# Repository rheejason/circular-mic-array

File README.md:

# Circular Beamforming Microphone Array

UIUC ECE 395: an 8-mic circular beamforming microphone array (steerable conference-table mic
and acoustic imager).

| Folder | What | Tooling |
|---|---|---|
| `firmware/nucleo-proto/` | Bench prototype: NUCLEO-H753ZI + 4 Adafruit PDM mics on a 3D-printed 45 mm ring | STM32CubeIDE |
| `firmware/final/` | Firmware for the custom 8-mic STM32H743 board | STM32CubeIDE |
| `firmware/common/` | Hardware-independent C shared by both: DOA (GCC-PHAT), beamformer, ring buffer | CMSIS-DSP |
| `hardware/kicad/` | 8-mic board: 8 × T5838 PDM mics → ADAU7118 → STM32H743 SAI | KiCad |
| `hardware/mechanical/` | Bench rig mount and enclosure (STEP / 3MF exports) | Fusion 360 |
| `hardware/bom/` | Bills of materials | |

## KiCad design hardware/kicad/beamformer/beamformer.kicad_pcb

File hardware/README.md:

# Hardware

| Folder | What |
|---|---|
| `kicad/` | 8-mic board KiCad project |
| `mechanical/` | Bench rig ring and enclosure: STEP and 3MF exports (keep the Fusion source link in a note here) |
| `bom/` | Bills of materials |
| `layout-checklist.md` | What's left before and during PCB layout, and before ordering |

## 8-mic board (planned)

- 8 × TDK InvenSense T5838 (MMICT5838-00-012), bottom port, uniform circle, radius 55 mm (tentative).
  Each mic needs a 0.5–1 mm PCB hole; the hole centre is the mic's acoustic position.
- 2 mics per PDM data line (opposite SELECT), 4 lines into an ADAU7118 → TDM8 → STM32H743 SAI.
- PDM clock 3.072 MHz (÷64 = 48 kHz).
- Still to decide: LCD part (round GC9A01 planned), LED ring, enclosure, which mics share a data line.
- Check in the datasheets before layout: ADAU7118 clocking and PDM clock fan-out, T5838 mode/threshold pins.

## KiCad

Schematic and PCB files don't merge, so only one person edits a sheet or board at a time.
Pull before opening KiCad and push when you're done.

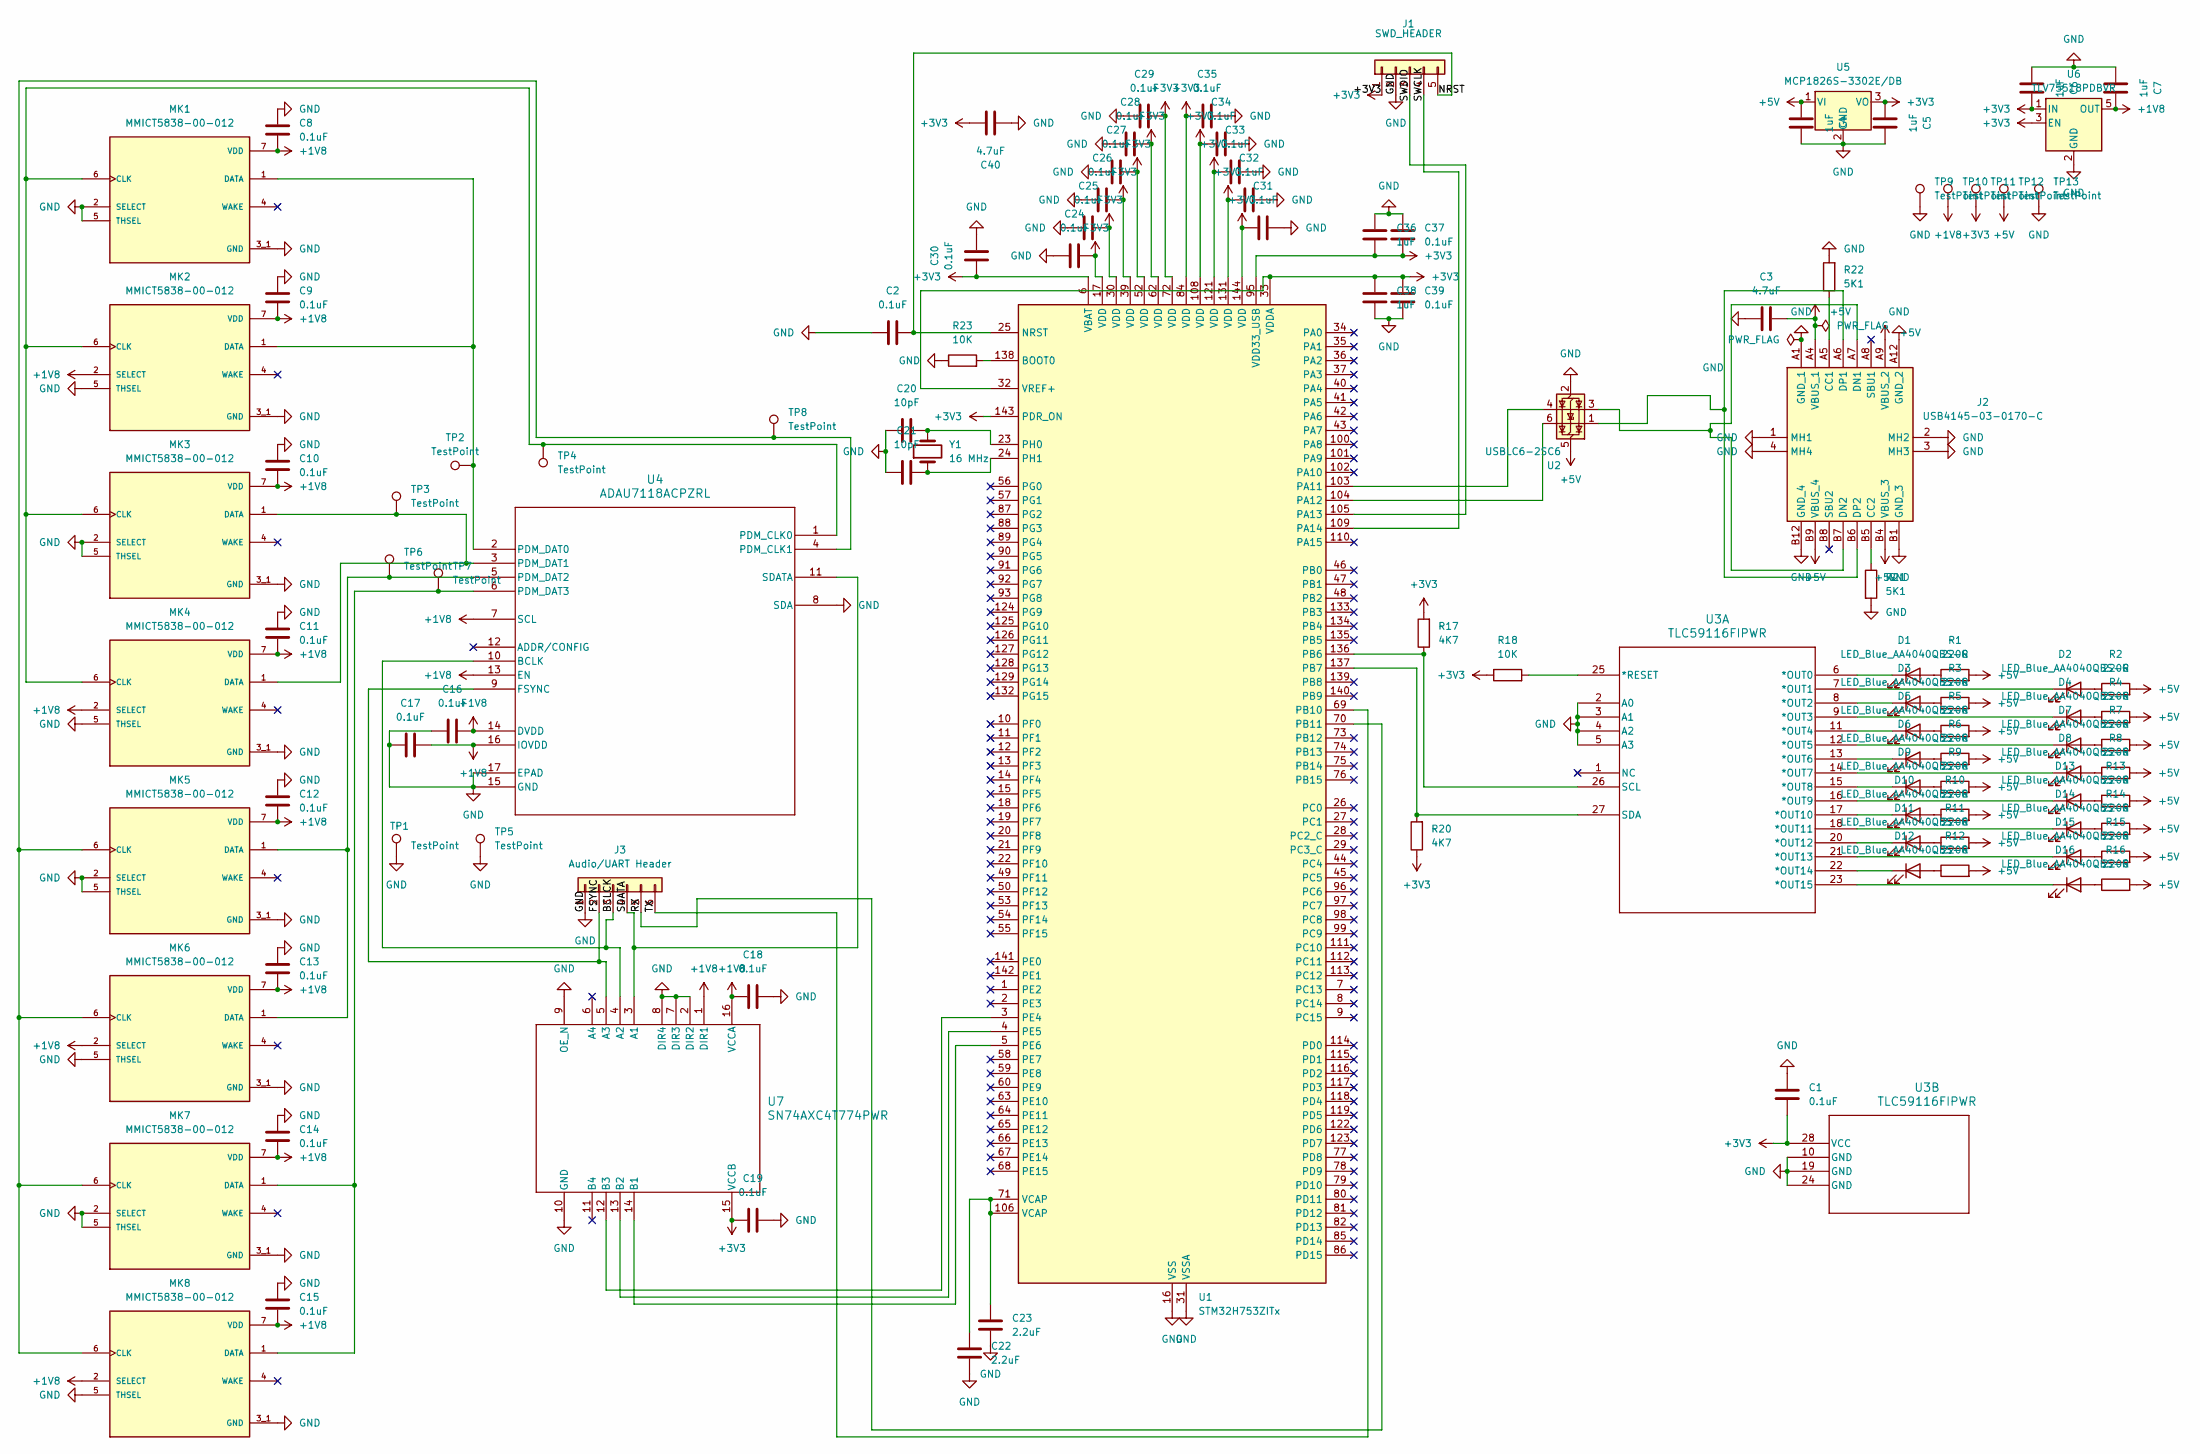
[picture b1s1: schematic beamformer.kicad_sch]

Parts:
C1, C2, C8, C9, C10, C11, C12, C13, C14, C15, C16, C17, C18, C19, C24, C25, C26, C27, C28, C29, C30, C31, C32, C33, C34, C35, C37, C39: 0.1uF; C_0805_2012Metric
C3, C40: 4.7uF; C_0805_2012Metric
C4, C5, C6, C7, C36, C38: 1uF; C_0805_2012Metric
C20, C21: 10pF; C_0805_2012Metric
C22, C23: 2.2uF; C_0805_2012Metric
D1, D2, D3, D4, D5, D6, D7, D8, D9, D10, D11, D12, D13, D14, D15, D16: LED_Blue_AA4040QBS-G; LED_Kingbright_AA4040QBS-G
J1: SWD_HEADER; PinHeader_1x05_P2.54mm_Vertical
J2: USB4145-03-0170-C; CONN_USB4145-03-0230-C_GCT; Manufacturer_Part_Number USB4145-03-0170-C; Mouser Part Number 640-USB4145-3-0170-C
J3: Audio/UART Header; PinHeader_1x06_P2.54mm_Vertical
MK1, MK2, MK3, MK4, MK5, MK6, MK7, MK8: MMICT5838-00-012; MIC_MMICT5838-00-012; PARTREV 1.1
R1, R2, R3, R4, R5, R6, R7, R8, R9, R10, R11, R12, R13, R14, R15, R16: 220R; R_0805_2012Metric
R17, R20: 4K7; R_0805_2012Metric
R18, R23: 10K; R_0805_2012Metric
R21, R22: 5K1; R_0805_2012Metric
TP1, TP2, TP3, TP4, TP5, TP6, TP7, TP8, TP9, TP10, TP11, TP12, TP13: TestPoint; TestPoint_Pad_D1.5mm
U1: STM32H753ZITx; LQFP-144_20x20mm_P0.5mm
U2: USBLC6-2SC6; SOT-23-6
U3: TLC59116FIPWR; TSSOP-28_4.4x9.7mm_P0.65mm
U4: ADAU7118ACPZRL; CP-16-22_ADI
U5: MCP1826S-3302E/DB; SOT-223-3_TabPin2
U6: TLV75518PDBVR; SOT-23-5
U7: SN74AXC4T774PWR; TSSOP-16_4.4x5mm_P0.65mm
Y1: 16 MHz; ECS-160-8-30Q-VY-TR

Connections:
+1V8: C7.2, C8.1, C9.1, C10.1, C11.1, C12.1, C13.1, C14.1, C15.1, C16.1, C17.1, C18.2, MK1.7 (VDD), MK2.2 (SELECT), MK2.7 (VDD), MK3.7 (VDD), MK4.2 (SELECT), MK4.7 (VDD), MK5.7 (VDD), MK6.2 (SELECT), MK6.7 (VDD), MK7.7 (VDD), MK8.2 (SELECT), MK8.7 (VDD), TP10.1 (1_1), U4.7 (SCL), U4.13 (EN), U4.14 (DVDD), U4.16 (IOVDD), U6.5 (OUT), U7.1 (DIR1), U7.16 (VCCA)
+3V3: C1.2, C5.1, C6.2, C19.2, C24.2, C25.2, C26.2, C27.2, C28.2, C29.2, C30.1, C31.2, C32.2, C33.2, C34.2, C35.2, C36.2, C37.2, C38.1, C39.1, C40.2, J1.1, R17.2, R18.1, R20.1, TP11.1 (1_1), U1.6 (VBAT), U1.17 (VDD), U1.30 (VDD), U1.32 (VREF+), U1.33 (VDDA), U1.39 (VDD), U1.52 (VDD), U1.62 (VDD), U1.72 (VDD), U1.84 (VDD), U1.95 (VDD33_USB), U1.108 (VDD), U1.121 (VDD), U1.131 (VDD), U1.143 (PDR_ON), U1.144 (VDD), U3.28 (VCC), U5.3 (VO), U6.1 (IN), U6.3 (EN), U7.15 (VCCB)
+5V: C3.2, C4.1, J2.A4 (VBUS_1), J2.A9 (VBUS_2), J2.B4 (VBUS_3), J2.B9 (VBUS_4), R1.2, R2.2, R3.2, R4.2, R5.2, R6.2, R7.2, R8.2, R9.2, R10.2, R11.2, R12.2, R13.2, R14.2, R15.2, R16.2, TP12.1 (1_1), U2.5 (VBUS), U5.1 (VI)
/BCLCK: J3.3, U4.10 (BCLK), U7.4 (A2)
/FSYNC: J3.2, U4.9 (FSYNC), U7.5 (A3)
/NRST: C2.2, J1.5, U1.25 (NRST)
/RX: J3.5, U1.70 (PB11)
/SDATA: J3.4, U4.11 (SDATA), U7.3 (A1)
/SWCLK: J1.4, U1.109 (PA14)
/SWDIO: J1.3, U1.105 (PA13)
/TX: J3.6, U1.69 (PB10)
GND: C1.1, C2.1, C3.1, C4.2, C5.2, C6.1, C7.1, C8.2, C9.2, C10.2, C11.2, C12.2, C13.2, C14.2, C15.2, C16.2, C17.2, C18.1, C19.1, C20.1, C21.1, C22.2, C23.2, C24.1, C25.1, C26.1, C27.1, C28.1, C29.1, C30.2, C31.1, C32.1, C33.1, C34.1, C35.1, C36.1, C37.1, C38.2, C39.2, C40.1, J1.2, J2.1 (MH1), J2.2 (MH2), J2.3 (MH3), J2.4 (MH4), J2.A1 (GND_1), J2.A12 (GND_2), J2.B1 (GND_3), J2.B12 (GND_4), J3.1, MK1.2 (SELECT), MK1.3_1 (GND), MK1.3_2 (GND), MK1.5 (THSEL), MK2.3_1 (GND), MK2.3_2 (GND), MK2.5 (THSEL), MK3.2 (SELECT), MK3.3_1 (GND), MK3.3_2 (GND), MK3.5 (THSEL), MK4.3_1 (GND), MK4.3_2 (GND), MK4.5 (THSEL), MK5.2 (SELECT), MK5.3_1 (GND), MK5.3_2 (GND), MK5.5 (THSEL), MK6.3_1 (GND), MK6.3_2 (GND), MK6.5 (THSEL), MK7.2 (SELECT), MK7.3_1 (GND), MK7.3_2 (GND), MK7.5 (THSEL), MK8.3_1 (GND), MK8.3_2 (GND), MK8.5 (THSEL), R21.2, R22.2, R23.1, TP1.1 (1_1), TP5.1 (1_1), TP9.1 (1_1), TP13.1 (1_1), U1.16 (VSS), U1.31 (VSSA), U1.38 (VSS), U1.51 (VSS), U1.61 (VSS), U1.83 (VSS), U1.94 (VSS), U1.107 (VSS), U1.120 (VSS), U1.130 (VSS), U2.2 (GND), U3.2 (A0), U3.3 (A1), U3.4 (A2), U3.5 (A3), U3.10 (GND), U3.19 (GND), U3.24 (GND), U4.8 (SDA), U4.15 (GND), U4.17 (EPAD), U5.2 (GND), U6.2 (GND), U7.2 (DIR2), U7.7 (DIR3), U7.8 (DIR4), U7.9 (OE_N), U7.10 (GND)
unnamed: C22.1, C23.1, U1.71 (VCAP), U1.106 (VCAP)
unnamed: D1.2 (A), R1.1
unnamed: D1.1 (K), U3.6 (*OUT0)
unnamed: D2.2 (A), R2.1
unnamed: D2.1 (K), U3.7 (*OUT1)
unnamed: D3.2 (A), R3.1
unnamed: D3.1 (K), U3.8 (*OUT2)
unnamed: D4.2 (A), R4.1
unnamed: D4.1 (K), U3.9 (*OUT3)
unnamed: D5.2 (A), R5.1
unnamed: D5.1 (K), U3.11 (*OUT4)
unnamed: D6.2 (A), R6.1
unnamed: D6.1 (K), U3.13 (*OUT6)
unnamed: D7.2 (A), R7.1
unnamed: D7.1 (K), U3.12 (*OUT5)
unnamed: D8.2 (A), R8.1
unnamed: D8.1 (K), U3.14 (*OUT7)
unnamed: D9.2 (A), R9.1
unnamed: D9.1 (K), U3.15 (*OUT8)
unnamed: D10.2 (A), R10.1
unnamed: D10.1 (K), U3.17 (*OUT10)
unnamed: D11.2 (A), R11.1
unnamed: D11.1 (K), U3.20 (*OUT12)
unnamed: D12.2 (A), R12.1
unnamed: D12.1 (K), U3.22 (*OUT14)
unnamed: D13.2 (A), R13.1
unnamed: D13.1 (K), U3.16 (*OUT9)
unnamed: D14.2 (A), R14.1
unnamed: D14.1 (K), U3.18 (*OUT11)
unnamed: D15.2 (A), R15.1
unnamed: D15.1 (K), U3.21 (*OUT13)
unnamed: D16.2 (A), R16.1
unnamed: D16.1 (K), U3.23 (*OUT15)
unnamed: J2.A5 (CC1), R22.1
unnamed: J2.B5 (CC2), R21.1
unnamed: J2.A7 (DN1), J2.B7 (DN2), U2.3 (I/O2)
unnamed: J2.A6 (DP1), J2.B6 (DP2), U2.1 (I/O1)
unnamed: MK1.6 (CLK), MK2.6 (CLK), MK3.6 (CLK), MK4.6 (CLK), TP4.1 (1_1), U4.1 (PDM_CLK0)
unnamed: MK1.1 (DATA), MK2.1 (DATA), TP2.1 (1_1), U4.2 (PDM_DAT0)
unnamed: MK3.1 (DATA), MK4.1 (DATA), TP3.1 (1_1), U4.3 (PDM_DAT1)
unnamed: MK5.6 (CLK), MK6.6 (CLK), MK7.6 (CLK), MK8.6 (CLK), TP8.1 (1_1), U4.4 (PDM_CLK1)
unnamed: MK5.1 (DATA), MK6.1 (DATA), TP6.1 (1_1), U4.5 (PDM_DAT2)
unnamed: MK7.1 (DATA), MK8.1 (DATA), TP7.1 (1_1), U4.6 (PDM_DAT3)
unnamed: R23.2, U1.138 (BOOT0)
unnamed: U1.103 (PA11), U2.4 (I/O2)
unnamed: U1.104 (PA12), U2.6 (I/O1)
unnamed: R17.1, U1.136 (PB6), U3.26 (SCL)
unnamed: R20.2, U1.137 (PB7), U3.27 (SDA)
unnamed: U1.3 (PE4), U7.12 (B3)
unnamed: U1.4 (PE5), U7.13 (B2)
unnamed: U1.5 (PE6), U7.14 (B1)
unnamed: C20.2, U1.23 (PH0), Y1.2
unnamed: C21.2, U1.24 (PH1), Y1.1
unnamed: R18.2, U3.25 (*RESET)

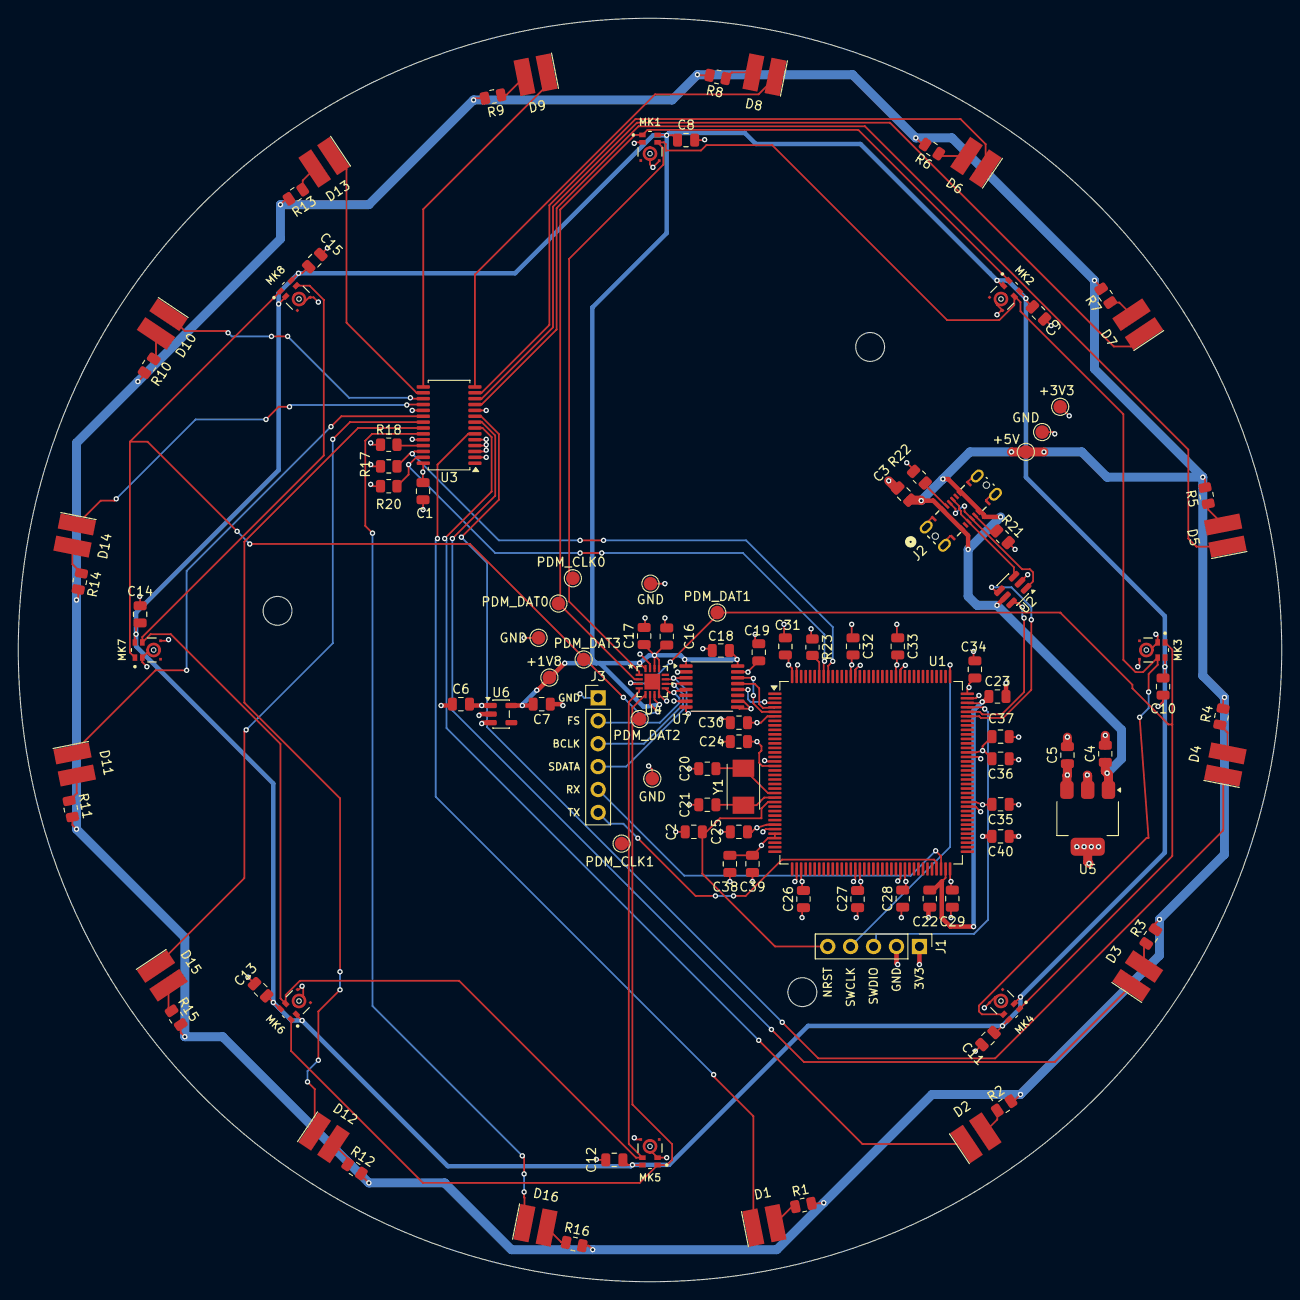
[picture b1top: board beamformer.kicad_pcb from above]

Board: 4 copper layers, 140.0 x 140.0 mm, 113 parts (0 on the bottom side), 66 nets.

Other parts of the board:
H1, H2, H3: MountingHole_3.2mm_M3

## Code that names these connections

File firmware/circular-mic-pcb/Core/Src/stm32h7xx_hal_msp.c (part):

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
    __HAL_RCC_GPIOB_CLK_ENABLE();
    /**I2C1 GPIO Configuration
    PB6     ------> I2C1_SCL
    PB7     ------> I2C1_SDA
    */
    GPIO_InitStruct.Pin = GPIO_PIN_6|GPIO_PIN_7;
    GPIO_InitStruct.Mode = GPIO_MODE_AF_OD;
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    __HAL_RCC_I2C1_CLK_DISABLE();

    /**I2C1 GPIO Configuration
    PB6     ------> I2C1_SCL
    PB7     ------> I2C1_SDA
    */
    HAL_GPIO_DeInit(GPIOB, GPIO_PIN_6);

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
    __HAL_RCC_GPIOB_CLK_ENABLE();
    /**USART3 GPIO Configuration
    PB10     ------> USART3_TX
    PB11     ------> USART3_RX
    */
    GPIO_InitStruct.Pin = GPIO_PIN_10|GPIO_PIN_11;
    GPIO_InitStruct.Mode = GPIO_MODE_AF_PP;
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    __HAL_RCC_USART3_CLK_DISABLE();

    /**USART3 GPIO Configuration
    PB10     ------> USART3_TX
    PB11     ------> USART3_RX
    */
    HAL_GPIO_DeInit(GPIOB, GPIO_PIN_10|GPIO_PIN_11);

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
    __HAL_RCC_GPIOA_CLK_ENABLE();
    /**USB_OTG_FS GPIO Configuration
    PA11     ------> USB_OTG_FS_DM
    PA12     ------> USB_OTG_FS_DP
    */
    GPIO_InitStruct.Pin = GPIO_PIN_11|GPIO_PIN_12;
    GPIO_InitStruct.Mode = GPIO_MODE_AF_PP;
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    __HAL_RCC_USB_OTG_FS_CLK_DISABLE();

    /**USB_OTG_FS GPIO Configuration
    PA11     ------> USB_OTG_FS_DM
    PA12     ------> USB_OTG_FS_DP
    */
    HAL_GPIO_DeInit(GPIOA, GPIO_PIN_11|GPIO_PIN_12);

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    SAI1_client ++;

    /**SAI1_A_Block_A GPIO Configuration
    PE4     ------> SAI1_FS_A
    PE5     ------> SAI1_SCK_A
    PE6     ------> SAI1_SD_A
    */
    GPIO_InitStruct.Pin = GPIO_PIN_4|GPIO_PIN_5;
    GPIO_InitStruct.Mode = GPIO_MODE_AF_PP;
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      }

    /**SAI1_A_Block_A GPIO Configuration
    PE4     ------> SAI1_FS_A
    PE5     ------> SAI1_SCK_A
    PE6     ------> SAI1_SD_A
    */
    HAL_GPIO_DeInit(GPIOE, GPIO_PIN_4|GPIO_PIN_5|GPIO_PIN_6);

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

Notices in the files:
firmware/circular-mic-pcb/Core/Src/stm32h7xx_hal_msp.c:
Copyright (c) 2026 STMicroelectronics.
All rights reserved.
This software is licensed under terms that can be found in the LICENSE file
